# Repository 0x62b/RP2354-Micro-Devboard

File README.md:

# RP2354-Micro-Devboard
A devboard based on the RP2354 in a small form factor. It is roughly the size of a Seeed Xiao RP2350, and it was going to be pin compatible, before I realised what a messy routing job that was going to be, so I switched the layout for something more logical.

This is probably just going to be used for some small boards that need an RP2350 but that I don't want to directly build the MCU into, without having to go acquire a Xiao, supermini, or something like that.

*many of the files are named as RP2350 because that is what I was using before

The board is compatible with any firmware written for the Pi Pico/RP2350, as long as they don't use the omitted GPIO pins anyway...

Note! The BOM.csv in project root is the LCSC exported BOM with links, while the BOM list in `production/` is the original 
KiCad exported BOM

# Features
* Based on RP2354A with 2MB onboard flash (small flash is a compromise for small size)
* 2 layer PCB (this killed my sanity)
* 10 GPIO outputs
* USB Micro B power/data connection
* a really REALLY messy PCB routing job (it passed DRC tho so I guess thats something...)

Zine page (yes the render is outdated)\

Finished schematic (I'm using the 2350A footprint because they're pin compatible)\

Finished PCB\

PCB render\

JLCPCB order\
Extra cost comes from lead-free HASL

LCSC order\

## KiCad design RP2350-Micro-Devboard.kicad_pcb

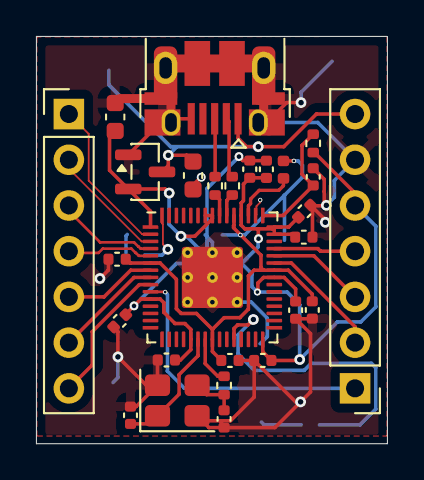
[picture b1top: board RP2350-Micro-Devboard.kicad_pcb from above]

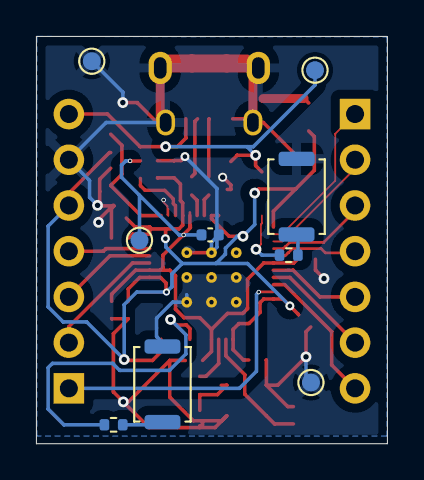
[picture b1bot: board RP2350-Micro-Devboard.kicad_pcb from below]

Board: 2 copper layers, 19.5 x 22.6 mm, 36 parts (9 on the bottom side), 28 nets.

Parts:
C1, C2, C3, C4, C5, C6, C7, C8, C10: 0.1uF; C_0402_1005Metric
C9, C15, C16, C17: 4.7uF; C_0402_1005Metric
C11, C12: 10uF; C_0603_1608Metric
C13, C14: 15pF; C_0402_1005Metric
J2, J3: Conn_01x07; PinHeader_1x07_P2.54mm_Vertical
J4: USB_B_Micro; USB_Micro-B_Amphenol_10103594-0001LF_Horizontal_modified
L1: 3.3uH; L_0402_1005Metric
R1, R2, R5: 1kΩ; R_0402_1005Metric
R3, R4: 27Ω; R_0402_1005Metric
R8: 33Ω; R_0402_1005Metric
SW1, SW2: SW_Push; SW_Push_SPST_NO_Alps_SKRK
TP1: VBUS; TestPoint_Pad_D1.0mm
TP2, TP5: GND; TestPoint_Pad_D1.0mm
TP4: 1V1; TestPoint_Pad_D1.0mm
U1: MCP1700x-330xxTT; SOT-23
U2: RP2350_60QFN; RP2350-QFN-60-1EP_7x7_P0.4mm_EP3.4x3.4mm_ThermalVias
Y1: 12MHz; Crystal_SMD_3225-4Pin_3.2x2.5mm

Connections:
+1V1: C8.1, C9.1, C10.1, C17.1, L1.1, TP4.1, U2.6 (DVDD), U2.23 (DVDD), U2.39 (DVDD), U2.50 (VREG_FB)
+3V3: C1.1, C2.1, C3.1, C4.1, C5.1, C6.1, C7.1, C12.1, C16.1, J3.5, R8.1, U1.2 (VO), U2.1 (IOVDD), U2.11 (IOVDD), U2.20 (IOVDD), U2.30 (IOVDD), U2.38 (IOVDD), U2.44 (ADC_AVDD), U2.45 (IOVDD), U2.49 (VREG_VIN), U2.53 (USB_OTP_VDD), U2.54 (QSPI_IOVDD)
/GPIO0: J2.1, U2.2 (GPIO0)
/GPIO1: J2.2, U2.3 (GPIO1)
/GPIO2: J2.3, U2.4 (GPIO2)
/GPIO3: J2.4, U2.5 (GPIO3)
/GPIO4: J2.5, U2.7 (GPIO4)
/GPIO5: J2.6, U2.8 (GPIO5)
/GPIO6: J2.7, U2.9 (GPIO6)
/GPIO7: J3.1, U2.10 (GPIO7)
/GPIO26: J3.2, U2.40 (GPIO26_ADC0)
/GPIO27: J3.3, U2.41 (GPIO27_ADC1)
/GPIO28: J3.4, U2.42 (GPIO28_ADC2)
/USB_D+: J4.3 (D+), R3.1
/USB_D-: J4.2 (D-), R4.1
/VBUS: C11.1, J3.7, J4.1 (VBUS), TP1.1, U1.3 (VI)
/VREG_AVDD: C15.1, R8.2, U2.46 (VREG_AVDD)
/VREG_LX: L1.2, U2.48 (VREG_LX)
/XIN: C13.1, U2.21 (XIN), Y1.1
/XOUT: R5.1, U2.22 (XOUT)
GND: C1.2, C2.2, C3.2, C4.2, C5.2, C6.2, C7.2, C8.2, C9.2, C10.2, C11.2, C12.2, C13.2, C14.2, C15.2, C16.2, C17.2, J3.6, J4.5 (GND), J4.6 (Shield), SW1.2, SW2.2, TP2.1, TP5.1, U1.1 (GND), U2.47 (VREG_PGND), U2.61 (GND), Y1.2 (G), Y1.4 (G)
unnamed: C14.1, R5.2, Y1.3
unnamed: R1.1, SW1.1
unnamed: R2.1, SW2.1
unnamed: R1.2, U2.60 (QSPI_SS)
unnamed: R2.2, U2.26 (RUN)
unnamed: R4.2, U2.51 (USB_DM)
unnamed: R3.2, U2.52 (USB_DP)

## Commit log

2026-04-04 broken
2026-04-04 first completion of shitty routing
2026-04-04 fix the drc
2026-04-04 readme
2026-04-04 gitignore
2026-04-04 add production files
2026-04-04 add 3d model
2026-04-04 symbol/footprint libraries
2026-04-04 more files
    i have no idea if you need this or if this even works
2026-04-04 add naming note
2026-04-04 more prod files
2026-04-04 fix and make consistent values
2026-04-04 add zine page
2026-04-04 Update README.md
    Proper line breaks
2026-04-04 new renders
2026-04-04 new production files
2026-04-04 add testpoints, add buttons
2026-04-04 new schematic + pcb screenshots
2026-04-04 fix file extension
2026-04-05 updated bom
2026-04-05 reviewer notes
2026-04-05 repo organisation
2026-04-05 bom note
2026-04-26 new zine page'
